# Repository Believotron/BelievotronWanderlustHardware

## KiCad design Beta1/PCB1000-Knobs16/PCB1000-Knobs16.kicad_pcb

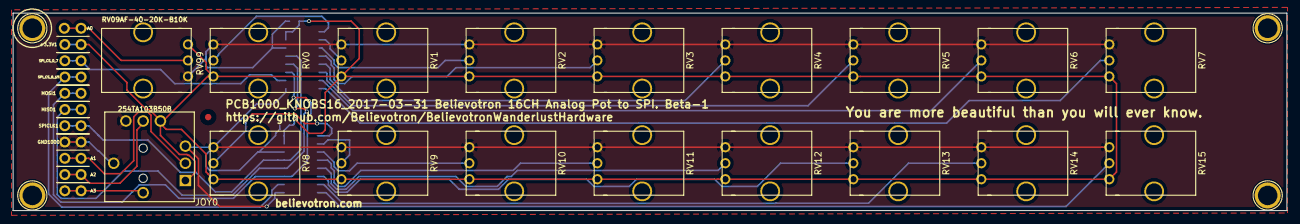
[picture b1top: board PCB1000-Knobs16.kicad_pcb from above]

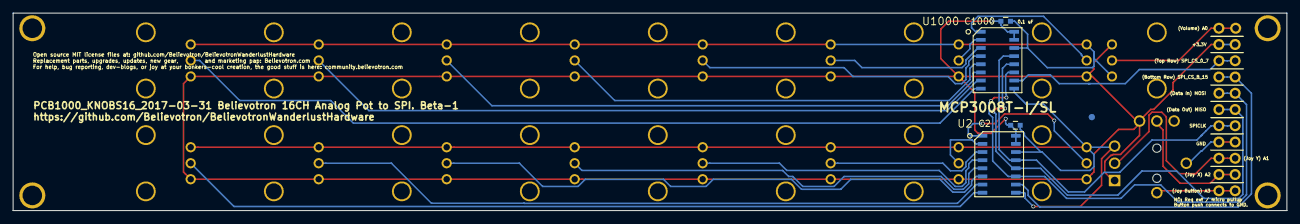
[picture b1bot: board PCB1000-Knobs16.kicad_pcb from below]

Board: 2 copper layers, 199.0 x 30.9 mm, 37 parts (4 on the bottom side), 27 nets.

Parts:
+3.3V1: CONN_01X01; TH_0.1_1x2_Jumper
A0, A0#2, A1, A1#2, A2, A2#2, A3, A3#2: CONN_01X01; single_0.1
C2, C1000: 0.1u; C_0603
GND1000: CONN_01X01; TH_0.1_1x2_Jumper
JOY0: XYJOY; XY_JOY_254TA103B50B
MISO1: CONN_01X01; TH_0.1_1x2_Jumper
MOSI1: CONN_01X01; TH_0.1_1x2_Jumper
RV0, RV1, RV2, RV3, RV4, RV5, RV6, RV7, RV8, RV9, RV10, RV11, RV12, RV13, RV14, RV15, RV99: POT; RV09AF-40-20K-B10K
SPICLK1: CONN_01X01; TH_0.1_1x2_Jumper
SPI_CS_0_7, SPI_CS_8_15: CONN_01X01; TH_0.1_1x2_Jumper
U2, U1000: MCP3008T-I/SL; SOIC-16

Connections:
+3V3: +3.3V1.1, C2.1, C1000.1, JOY0.R1.1, JOY0.R2.1, RV0.1, RV1.1, RV2.1, RV3.1, RV4.1, RV5.1, RV6.1, RV7.1, RV8.1, RV9.1, RV10.1, RV11.1, RV12.1, RV13.1, RV14.1, RV15.1, RV99.1, U2.15, U2.16, U1000.15, U1000.16
/CS_LED_8_15: SPI_CS_8_15.1, U2.10
/CS_R0_7: SPI_CS_0_7.1, U1000.10
/MISO: MISO1.1, U2.12, U1000.12
/MOSI: MOSI1.1, U2.11, U1000.11
/P0: RV0.2, U1000.1
/P1: RV1.2, U1000.2
/P2: RV2.2, U1000.3
/P3: RV3.2, U1000.4
/P4: RV4.2, U1000.5
/P5: RV5.2, U1000.6
/P6: RV6.2, U1000.7
/P7: RV7.2, U1000.8
/P8: RV8.2, U2.1
/P9: RV9.2, U2.2
/P10: RV10.2, U2.3
/P11: RV11.2, U2.4
/P12: RV12.2, U2.5
/P13: RV13.2, U2.6
/P14: RV14.2, U2.7
/P15: RV15.2, U2.8
/SPICLK: SPICLK1.1, U2.13, U1000.13
/VOLUME: A0.1, A0#2.1, RV99.2
GND: C2.2, C1000.2, GND1000.1, JOY0.R1.3, JOY0.R2.3, JOY0.S1.1, RV0.3, RV1.3, RV2.3, RV3.3, RV4.3, RV5.3, RV6.3, RV7.3, RV8.3, RV9.3, RV10.3, RV11.3, RV12.3, RV13.3, RV14.3, RV15.3, RV99.3, U2.9, U2.14, U1000.9, U1000.14
unnamed: A1.1, A1#2.1, JOY0.R1.2
unnamed: A2.1, A2#2.1, JOY0.R2.2
unnamed: A3.1, A3#2.1, JOY0.S1.2

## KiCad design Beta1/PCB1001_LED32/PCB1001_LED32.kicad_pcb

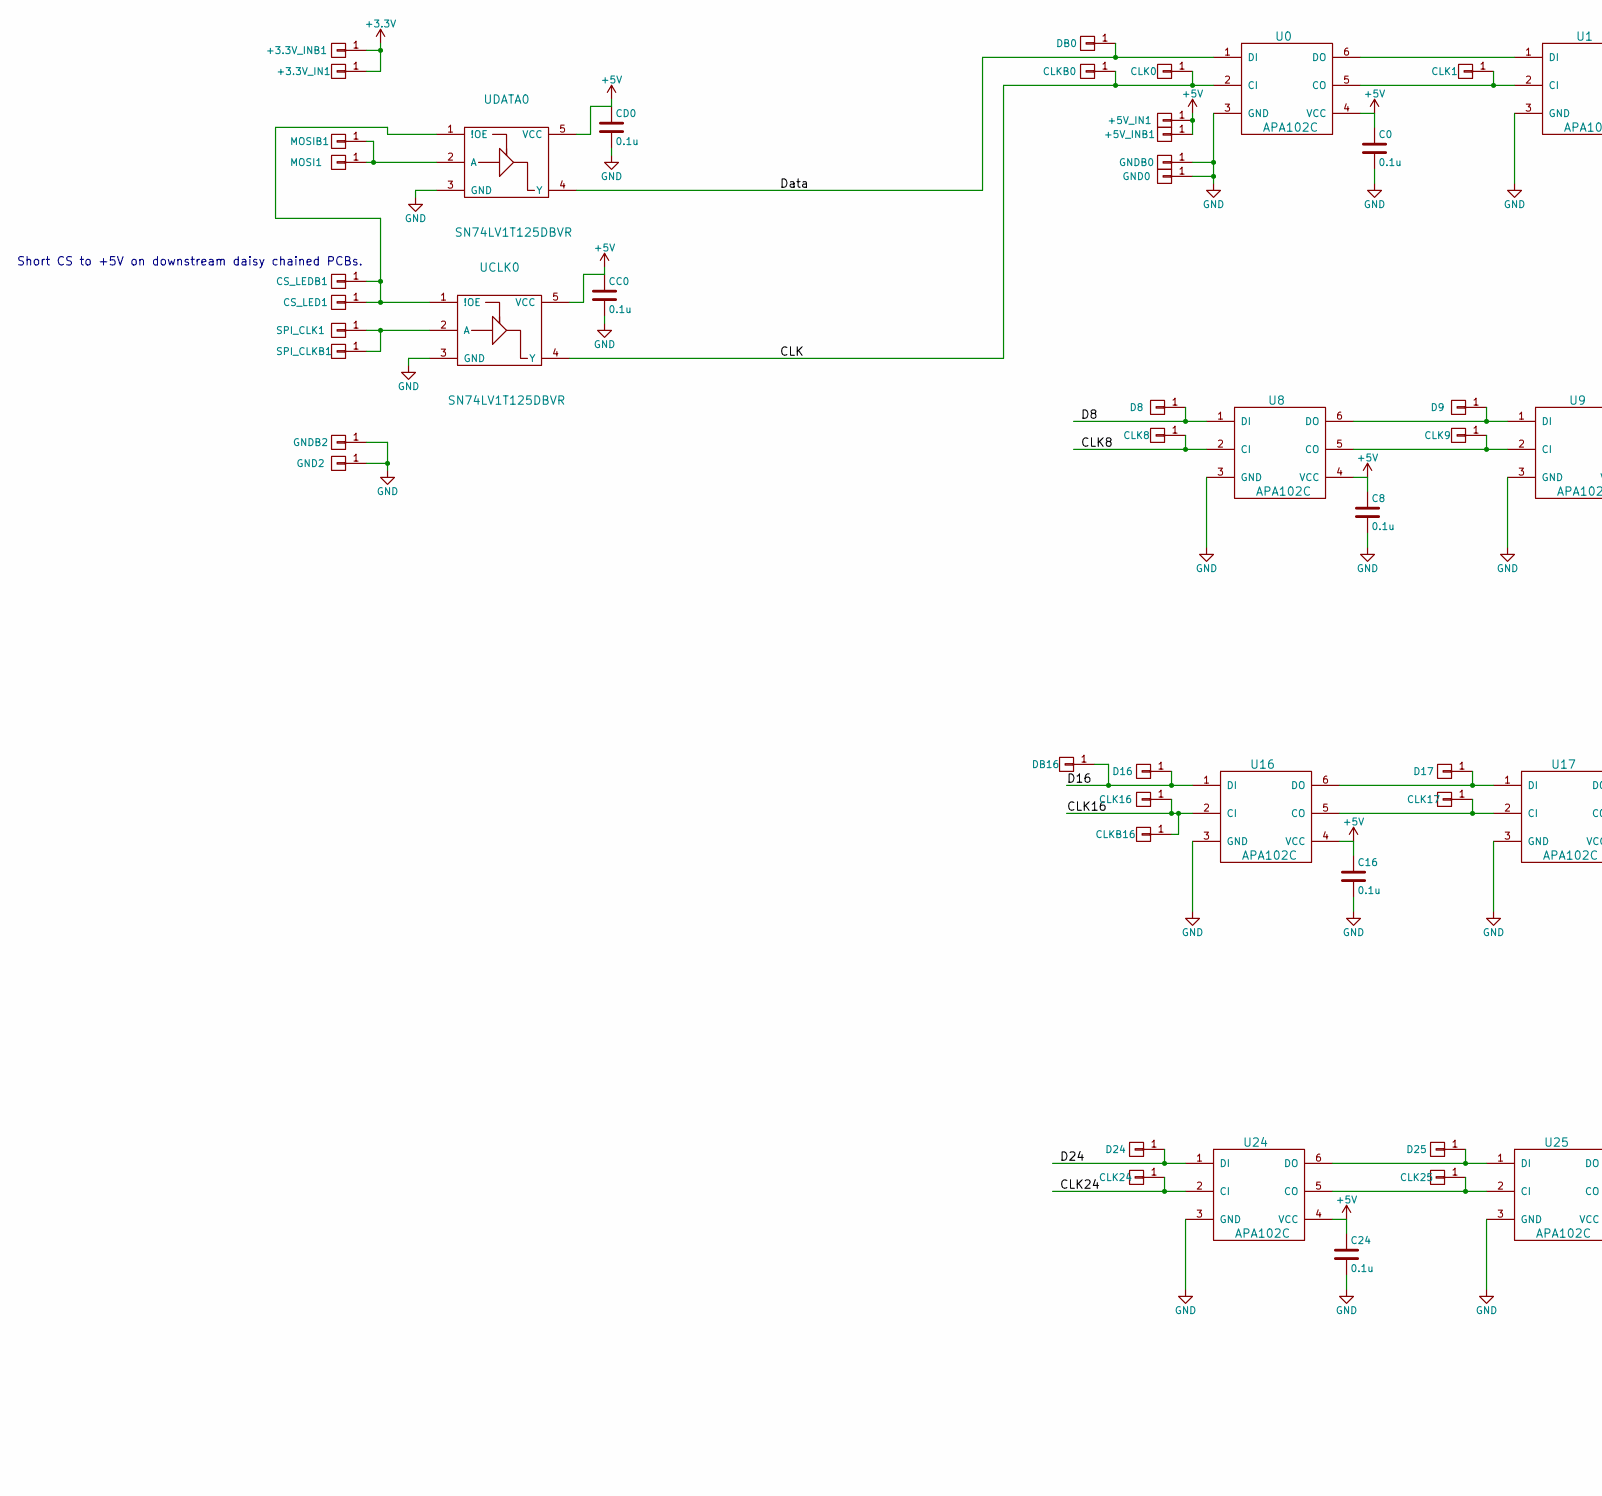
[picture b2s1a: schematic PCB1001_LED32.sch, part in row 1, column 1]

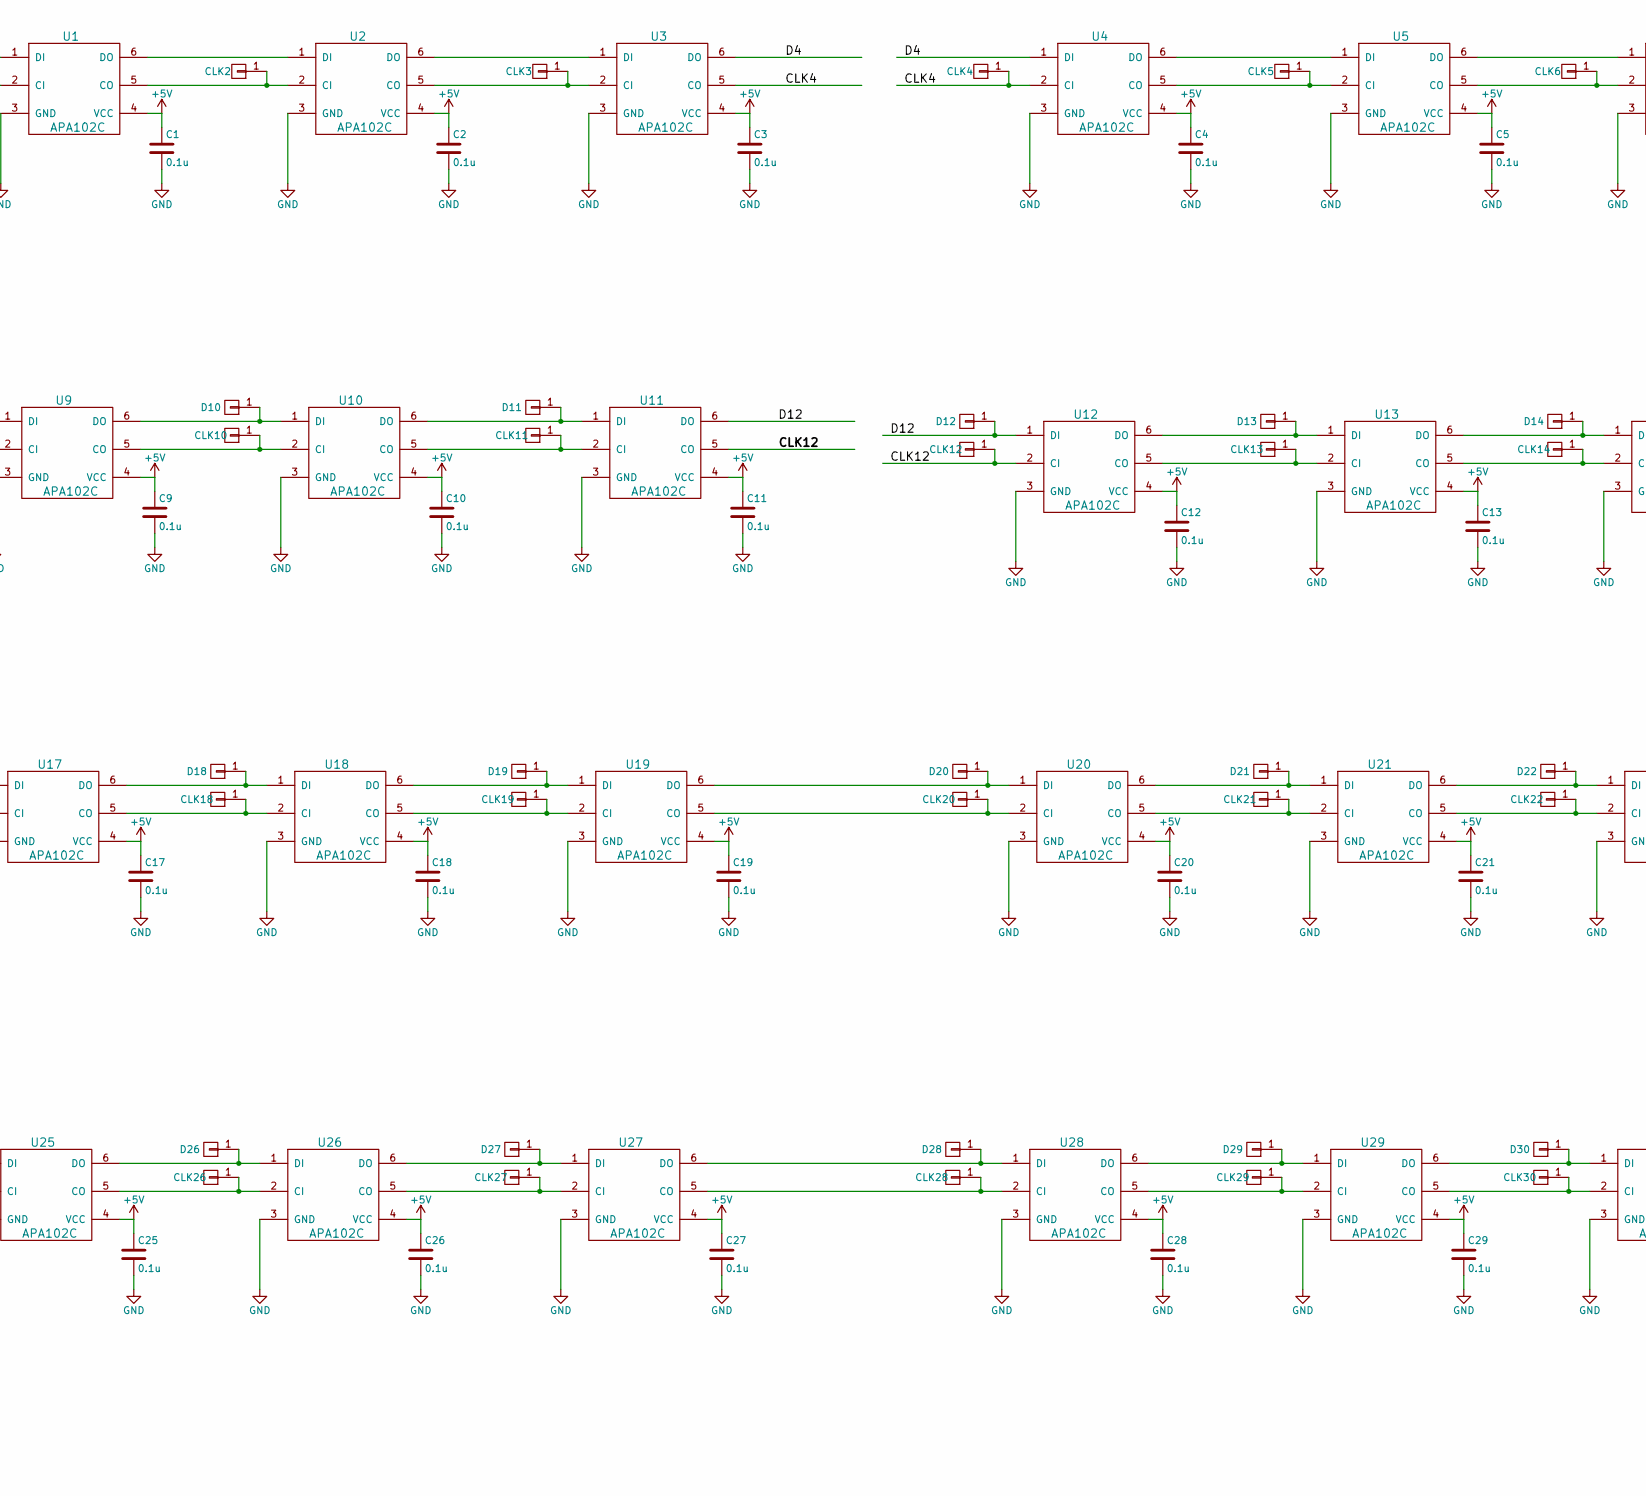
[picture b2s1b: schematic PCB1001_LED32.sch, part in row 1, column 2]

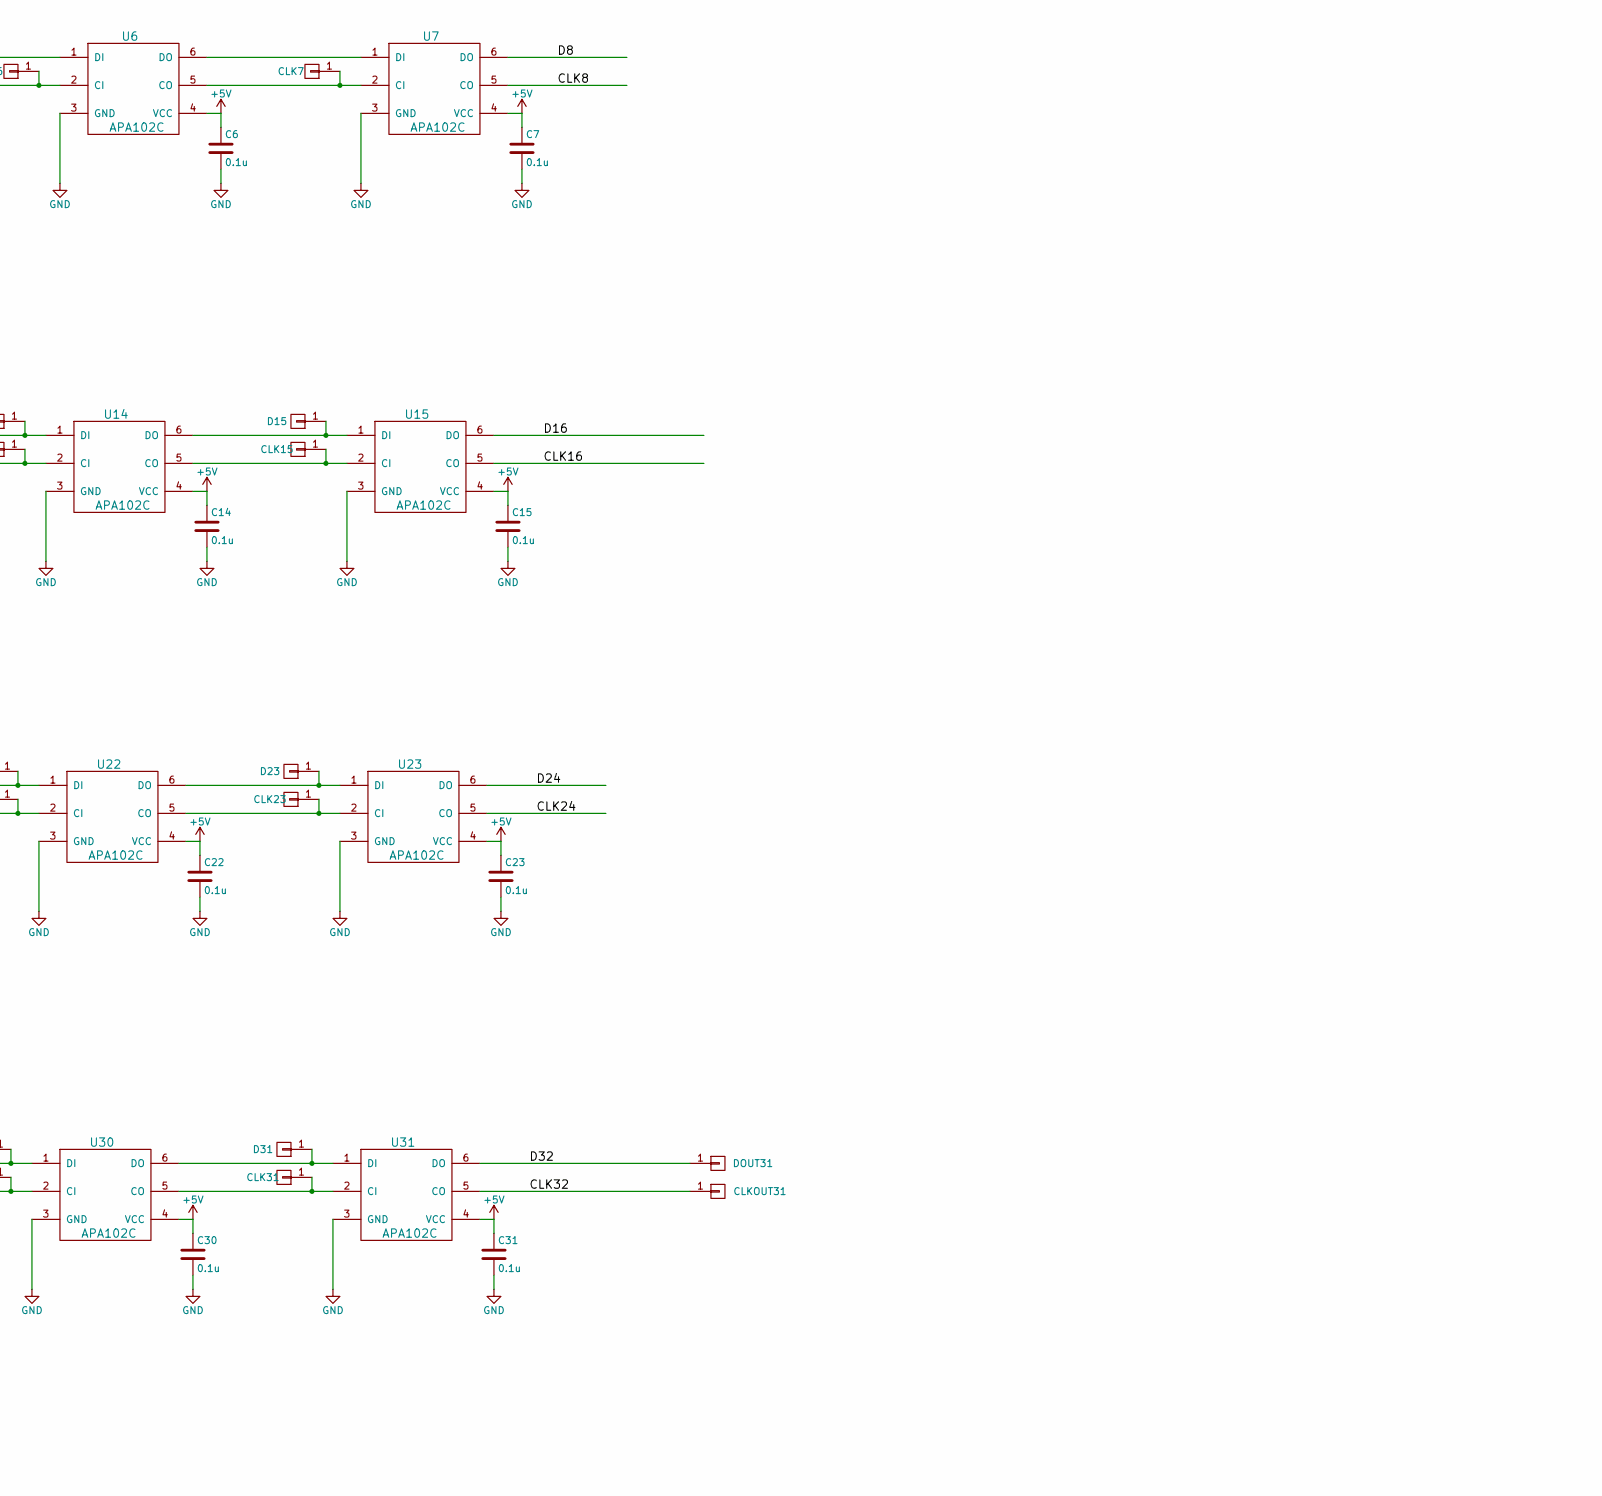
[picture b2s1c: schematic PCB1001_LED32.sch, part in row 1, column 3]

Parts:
+3.3V_IN1, +3.3V_INB1, +5V_IN1, +5V_INB1: CONN_01X01; single_0.1; MPN ON_PCB
C0, C1, C2, C3, C4, C5, C6, C7, C8, C9, C10, C11, C12, C13, C14, C15, C16, C17, C18, C19, C20, C21, C22, C23, C24, C25, C26, C27, C28, C29, C30, C31: 0.1u; C_0603; MPN CC0603KRX7R9BB104
CC0: 0.1u; C_0603; MPN CC0603KRX7R9BB104
CD0: 0.1u; C_0603; MPN CC0603KRX7R9BB104
CLK0, CLK16: CONN_01X01; single_0.1; MPN ON_PCB
CLK1, CLK2, CLK3, CLK4, CLK5, CLK6, CLK7, CLK8, CLK9, CLK10, CLK11, CLK12, CLK13, CLK14, CLK15, CLK17, CLK18, CLK19, CLK20, CLK21, CLK22, CLK23, CLK24, CLK25, CLK26, CLK27, CLK28, CLK29, CLK30, CLK31: CONN_01X01; TESTPAD; MPN ON_PCB
CLKB0, CLKB16: CONN_01X01; single_0.1; MPN ON_PCB
CLKOUT31: CONN_01X01; single_0.1; MPN ON_PCB
CS_LED1: CONN_01X01; single_0.1; MPN ON_PCB
CS_LEDB1: CONN_01X01; single_0.1; MPN ON_PCB
D8, D9, D10, D11, D12, D13, D14, D15, D17, D18, D19, D20, D21, D22, D23, D24, D25, D26, D27, D28, D29, D30, D31: CONN_01X01; TESTPAD; MPN ON_PCB
D16: CONN_01X01; single_0.1; MPN ON_PCB
DB0, DB16: CONN_01X01; single_0.1; MPN ON_PCB
DOUT31: CONN_01X01; single_0.1; MPN ON_PCB
GND0, GND2: CONN_01X01; single_0.1; MPN ON_PCB
GNDB0, GNDB2: CONN_01X01; single_0.1; MPN ON_PCB
MOSI1: CONN_01X01; single_0.1; MPN ON_PCB
MOSIB1: CONN_01X01; single_0.1; MPN ON_PCB
SPI_CLK1: CONN_01X01; single_0.1; MPN ON_PCB
SPI_CLKB1: CONN_01X01; single_0.1; MPN ON_PCB
U0, U1, U2, U3, U4, U5, U6, U7, U8, U9, U10, U11, U12, U13, U14, U15, U16, U17, U18, U19, U20, U21, U22, U23, U24, U25, U26, U27, U28, U29, U30, U31: APA102C; PLCC6-1.6x4.2_LED; MPN APA102C
UCLK0: SN74LV1T125DBVR; SOT23-5; MPN SN74LV1T125DBVR
UDATA0: SN74LV1T125DBVR; SOT23-5; MPN SN74LV1T125DBVR

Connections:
+3V3: +3.3V_IN1.1, +3.3V_INB1.1
+5V: +5V_IN1.1, +5V_INB1.1, C0.1, C1.1, C2.1, C3.1, C4.1, C5.1, C6.1, C7.1, C8.1, C9.1, C10.1, C11.1, C12.1, C13.1, C14.1, C15.1, C16.1, C17.1, C18.1, C19.1, C20.1, C21.1, C22.1, C23.1, C24.1, C25.1, C26.1, C27.1, C28.1, C29.1, C30.1, C31.1, CC0.1, CD0.1, U0.4 (VCC), U1.4 (VCC), U2.4 (VCC), U3.4 (VCC), U4.4 (VCC), U5.4 (VCC), U6.4 (VCC), U7.4 (VCC), U8.4 (VCC), U9.4 (VCC), U10.4 (VCC), U11.4 (VCC), U12.4 (VCC), U13.4 (VCC), U14.4 (VCC), U15.4 (VCC), U16.4 (VCC), U17.4 (VCC), U18.4 (VCC), U19.4 (VCC), U20.4 (VCC), U21.4 (VCC), U22.4 (VCC), U23.4 (VCC), U24.4 (VCC), U25.4 (VCC), U26.4 (VCC), U27.4 (VCC), U28.4 (VCC), U29.4 (VCC), U30.4 (VCC), U31.4 (VCC), UCLK0.5 (VCC), UDATA0.5 (VCC)
/CLK: CLK0.1, CLKB0.1, U0.2 (CI), UCLK0.4 (Y)
/CLK4: CLK4.1, U3.5 (CO), U4.2 (CI)
/CLK8: CLK8.1, U7.5 (CO), U8.2 (CI)
/CLK12: CLK12.1, U11.5 (CO), U12.2 (CI)
/CLK16: CLK16.1, CLKB16.1, U15.5 (CO), U16.2 (CI)
/CLK24: CLK24.1, U23.5 (CO), U24.2 (CI)
/CLK32: CLKOUT31.1, U31.5 (CO)
/D4: U3.6 (DO), U4.1 (DI); also elsewhere on the board
/D8: D8.1, U7.6 (DO), U8.1 (DI)
/D12: D12.1, U11.6 (DO), U12.1 (DI)
/D16: D16.1, DB16.1, U15.6 (DO), U16.1 (DI)
/D24: D24.1, U23.6 (DO), U24.1 (DI)
/D32: DOUT31.1, U31.6 (DO)
/Data: DB0.1, U0.1 (DI), UDATA0.4 (Y); also elsewhere on the board
GND: C0.2, C1.2, C2.2, C3.2, C4.2, C5.2, C6.2, C7.2, C8.2, C9.2, C10.2, C11.2, C12.2, C13.2, C14.2, C15.2, C16.2, C17.2, C18.2, C19.2, C20.2, C21.2, C22.2, C23.2, C24.2, C25.2, C26.2, C27.2, C28.2, C29.2, C30.2, C31.2, CC0.2, CD0.2, GND0.1, GND2.1, GNDB0.1, GNDB2.1, U0.3 (GND), U1.3 (GND), U2.3 (GND), U3.3 (GND), U4.3 (GND), U5.3 (GND), U6.3 (GND), U7.3 (GND), U8.3 (GND), U9.3 (GND), U10.3 (GND), U11.3 (GND), U12.3 (GND), U13.3 (GND), U14.3 (GND), U15.3 (GND), U16.3 (GND), U17.3 (GND), U18.3 (GND), U19.3 (GND), U20.3 (GND), U21.3 (GND), U22.3 (GND), U23.3 (GND), U24.3 (GND), U25.3 (GND), U26.3 (GND), U27.3 (GND), U28.3 (GND), U29.3 (GND), U30.3 (GND), U31.3 (GND), UCLK0.3 (GND), UDATA0.3 (GND); also elsewhere on the board
unnamed: CLK1.1, U0.5 (CO), U1.2 (CI)
unnamed: CLK2.1, U1.5 (CO), U2.2 (CI)
unnamed: CLK3.1, U2.5 (CO), U3.2 (CI)
unnamed: CLK5.1, U4.5 (CO), U5.2 (CI)
unnamed: CLK6.1, U5.5 (CO), U6.2 (CI)
unnamed: CLK7.1, U6.5 (CO), U7.2 (CI)
unnamed: CLK9.1, U8.5 (CO), U9.2 (CI)
unnamed: CLK10.1, U9.5 (CO), U10.2 (CI)
unnamed: CLK11.1, U10.5 (CO), U11.2 (CI)
unnamed: CLK13.1, U12.5 (CO), U13.2 (CI)
unnamed: CLK14.1, U13.5 (CO), U14.2 (CI)
unnamed: CLK15.1, U14.5 (CO), U15.2 (CI)
unnamed: CLK17.1, U16.5 (CO), U17.2 (CI)
unnamed: CLK18.1, U17.5 (CO), U18.2 (CI)
unnamed: CLK19.1, U18.5 (CO), U19.2 (CI)
unnamed: CLK20.1, U19.5 (CO), U20.2 (CI)
unnamed: CLK21.1, U20.5 (CO), U21.2 (CI)
unnamed: CLK22.1, U21.5 (CO), U22.2 (CI)
unnamed: CLK23.1, U22.5 (CO), U23.2 (CI)
unnamed: CLK25.1, U24.5 (CO), U25.2 (CI)
unnamed: CLK26.1, U25.5 (CO), U26.2 (CI)
unnamed: CLK27.1, U26.5 (CO), U27.2 (CI)
unnamed: CLK28.1, U27.5 (CO), U28.2 (CI)
unnamed: CLK29.1, U28.5 (CO), U29.2 (CI)
unnamed: CLK30.1, U29.5 (CO), U30.2 (CI)
unnamed: CLK31.1, U30.5 (CO), U31.2 (CI)
unnamed 43: CS_LED1.1, CS_LEDB1.1, UCLK0.1 (!OE), UDATA0.1 (!OE); also elsewhere on the board
unnamed 44: U0.6 (DO), U1.1 (DI); also elsewhere on the board
unnamed 45: U1.6 (DO), U2.1 (DI); also elsewhere on the board
unnamed 46: U2.6 (DO), U3.1 (DI); also elsewhere on the board
unnamed 47: U4.6 (DO), U5.1 (DI); also elsewhere on the board
unnamed 48: U5.6 (DO), U6.1 (DI); also elsewhere on the board
unnamed 49: U6.6 (DO), U7.1 (DI); also elsewhere on the board
unnamed: D9.1, U8.6 (DO), U9.1 (DI)
unnamed: D10.1, U9.6 (DO), U10.1 (DI)
unnamed: D11.1, U10.6 (DO), U11.1 (DI)
unnamed: D13.1, U12.6 (DO), U13.1 (DI)
unnamed: D14.1, U13.6 (DO), U14.1 (DI)
unnamed: D15.1, U14.6 (DO), U15.1 (DI)
unnamed: D17.1, U16.6 (DO), U17.1 (DI)
unnamed: D18.1, U17.6 (DO), U18.1 (DI)
unnamed: D19.1, U18.6 (DO), U19.1 (DI)
unnamed: D20.1, U19.6 (DO), U20.1 (DI)
unnamed: D21.1, U20.6 (DO), U21.1 (DI)
unnamed: D22.1, U21.6 (DO), U22.1 (DI)
unnamed: D23.1, U22.6 (DO), U23.1 (DI)
unnamed: D25.1, U24.6 (DO), U25.1 (DI)
unnamed: D26.1, U25.6 (DO), U26.1 (DI)
unnamed: D27.1, U26.6 (DO), U27.1 (DI)
unnamed: D28.1, U27.6 (DO), U28.1 (DI)
unnamed: D29.1, U28.6 (DO), U29.1 (DI)
unnamed: D30.1, U29.6 (DO), U30.1 (DI)
unnamed: D31.1, U30.6 (DO), U31.1 (DI)
unnamed: MOSI1.1, MOSIB1.1, UDATA0.2 (A)
unnamed: SPI_CLK1.1, SPI_CLKB1.1, UCLK0.2 (A)

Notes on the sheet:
Files and Open source MIT License: github.com/Believotron/BelievotronWanderlustHardware Marketing Pap: Believotron.com The good stuff: community.believotron.com
Believotron Wanderlust 32 CH RGB LED PCB
2017-03-31
DATE
Author: Dazzling Duke of Lazers
Short CS to +5V on downstream daisy chained PCBs.

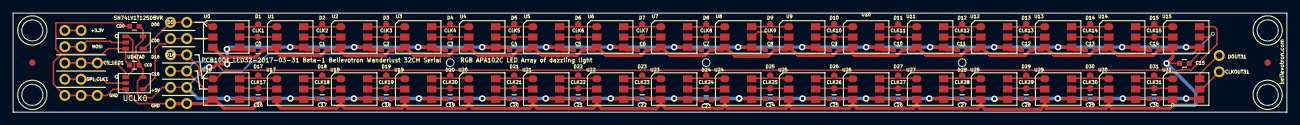
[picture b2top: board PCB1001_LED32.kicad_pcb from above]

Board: 2 copper layers, 199.0 x 15.5 mm, 153 parts (0 on the bottom side), 72 nets.

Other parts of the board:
CS_LED1#2: CONN_01X01; single_0.1
D0: CONN_01X01; single_0.1
D1, D2, D3, D4, D5, D6, D7: CONN_01X01; TESTPAD
GNDB2#2: CONN_01X01; single_0.1

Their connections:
/D4: D4.1; also elsewhere on the board
/Data: D0.1; also elsewhere on the board
GND: GNDB2#2.1; also elsewhere on the board
unnamed 43: CS_LED1#2.1; also elsewhere on the board
unnamed 44: D1.1; also elsewhere on the board
unnamed 45: D2.1; also elsewhere on the board
unnamed 46: D3.1; also elsewhere on the board
unnamed 47: D5.1; also elsewhere on the board
unnamed 48: D6.1; also elsewhere on the board
unnamed 49: D7.1; also elsewhere on the board

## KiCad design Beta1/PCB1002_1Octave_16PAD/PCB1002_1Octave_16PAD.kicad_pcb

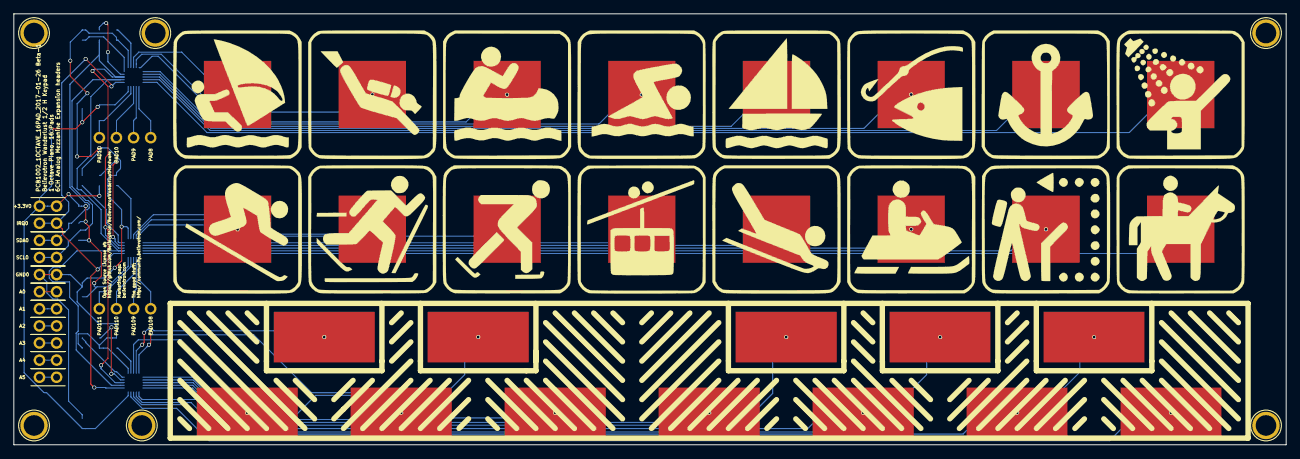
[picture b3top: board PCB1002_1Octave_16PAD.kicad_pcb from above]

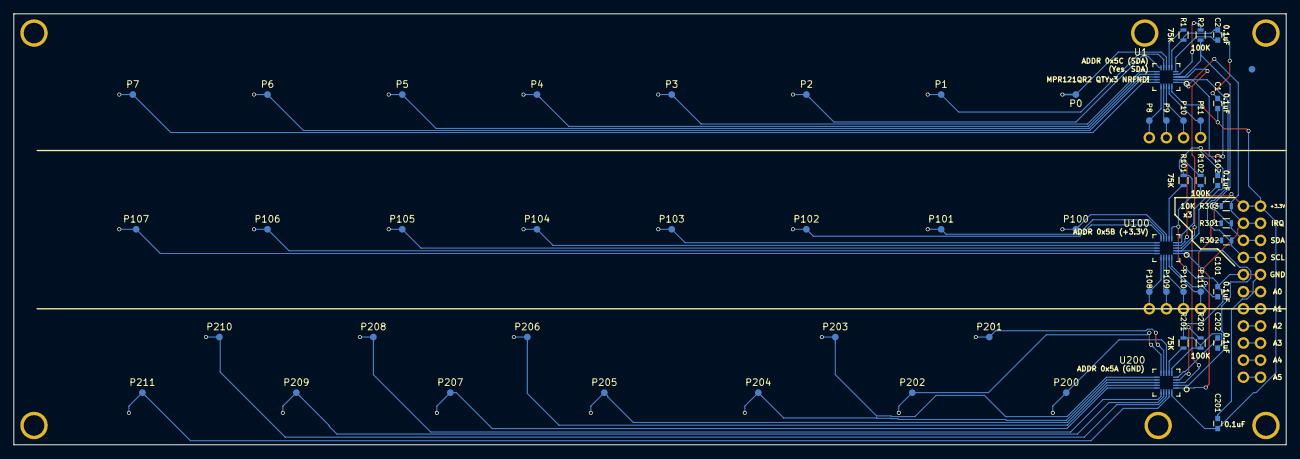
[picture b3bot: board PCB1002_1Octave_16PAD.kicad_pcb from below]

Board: 2 copper layers, 188.9 x 64.0 mm, 90 parts (54 on the bottom side), 50 nets.

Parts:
+3.3V0: CONN_01X01; TH_0.1_1x2_Jumper
A0, A1, A2, A3, A4, A5: CONN_01X01; TH_0.1_1x2_Jumper
C1, C101, C201: CC0603KRX7R9BB104; C_0603
C2, C102, C202: 0.1uf; C_0603
GND0: CONN_01X01; TH_0.1_1x2_Jumper
IRQ0: CONN_01X01; TH_0.1_1x2_Jumper
P0, P1, P2, P3, P4, P5, P6, P7, P8, P9, P10, P11, P100, P101, P102, P103, P104, P105, P106, P107, P108, P109, P110, P111, P200, P201, P202, P203, P204, P205, P206, P207, P208, P209, P210, P211: CONN_01X01; TESTPAD
PAD0, PAD1, PAD2, PAD3, PAD4, PAD5, PAD6, PAD7, PAD100, PAD101, PAD102, PAD103, PAD104, PAD105, PAD106, PAD107: TOUCHPAD_10CM; TOUCH_PAD_10CM
PAD8, PAD9, PAD10, PAD11, PAD108, PAD109, PAD110, PAD111: CONN_01X01; single_0.1
R1, R101, R201: 75K; R_0603
R2, R102, R202: 100K; R_0603
R301, R302, R303: 10K; R_0603
SCL0: CONN_01X01; TH_0.1_1x2_Jumper
SDA0: CONN_01X01; TH_0.1_1x2_Jumper
U1, U100, U200: MPR121QR2; QFN-20-1EP_3x3mm_Pitch0.40mm
UKEY0: KEYBOARD_1OCT; Keyboard_1_Octave_20CM

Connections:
+3V3: +3.3V0.1, C1.1, C101.1, C201.1, R102.1, R301.1, R302.1, R303.1, U1.20, U100.20, U200.20
/IRQ: IRQ0.1, R303.2, U1.1, U100.1, U200.1
/PAD0: P0.1, PAD0.1, U1.8
/PAD1: P1.1, PAD1.1, U1.9
/PAD2: P2.1, PAD2.1, U1.10
/PAD3: P3.1, PAD3.1, U1.11
/PAD4: P4.1, PAD4.1, U1.12
/PAD5: P5.1, PAD5.1, U1.13
/PAD6: P6.1, PAD6.1, U1.14
/PAD7: P7.1, PAD7.1, U1.15
/SCL: R302.2, SCL0.1, U1.2, U100.2, U200.2
/SDA: R2.1, R301.2, SDA0.1, U1.3, U100.3, U200.3
GND: C1.2, C2.2, C101.2, C102.2, C201.2, C202.2, GND0.1, R1.2, R101.2, R201.2, R202.1, U1.6, U100.6, U200.6
unnamed: C2.1, U1.5
unnamed: C102.1, U100.5
unnamed: C202.1, U200.5
unnamed: P8.1, PAD8.1, U1.16
unnamed: P9.1, PAD9.1, U1.17
unnamed: P10.1, PAD10.1, U1.18
unnamed: P11.1, PAD11.1, U1.19
unnamed: P100.1, PAD100.1, U100.8
unnamed: P101.1, PAD101.1, U100.9
unnamed: P102.1, PAD102.1, U100.10
unnamed: P103.1, PAD103.1, U100.11
unnamed: P104.1, PAD104.1, U100.12
unnamed: P105.1, PAD105.1, U100.13
unnamed: P106.1, PAD106.1, U100.14
unnamed: P107.1, PAD107.1, U100.15
unnamed: P108.1, PAD108.1, U100.16
unnamed: P109.1, PAD109.1, U100.17
unnamed: P110.1, PAD110.1, U100.18
unnamed: P111.1, PAD111.1, U100.19
unnamed: P200.1, U200.8, UKEY0.1
unnamed: P201.1, U200.9, UKEY0.2
unnamed: P202.1, U200.10, UKEY0.3
unnamed: P203.1, U200.11, UKEY0.4
unnamed: P204.1, U200.12, UKEY0.5
unnamed: P205.1, U200.13, UKEY0.6
unnamed: P206.1, U200.14, UKEY0.7
unnamed: P207.1, U200.15, UKEY0.8
unnamed: P208.1, U200.16, UKEY0.9
unnamed: P209.1, U200.17, UKEY0.10
unnamed: P210.1, U200.18, UKEY0.11
unnamed: P211.1, U200.19, UKEY0.12
unnamed: R1.1, U1.7
unnamed: R2.2, U1.4
unnamed: R101.1, U100.7
unnamed: R102.2, U100.4
unnamed: R201.1, U200.7
unnamed: R202.2, U200.4

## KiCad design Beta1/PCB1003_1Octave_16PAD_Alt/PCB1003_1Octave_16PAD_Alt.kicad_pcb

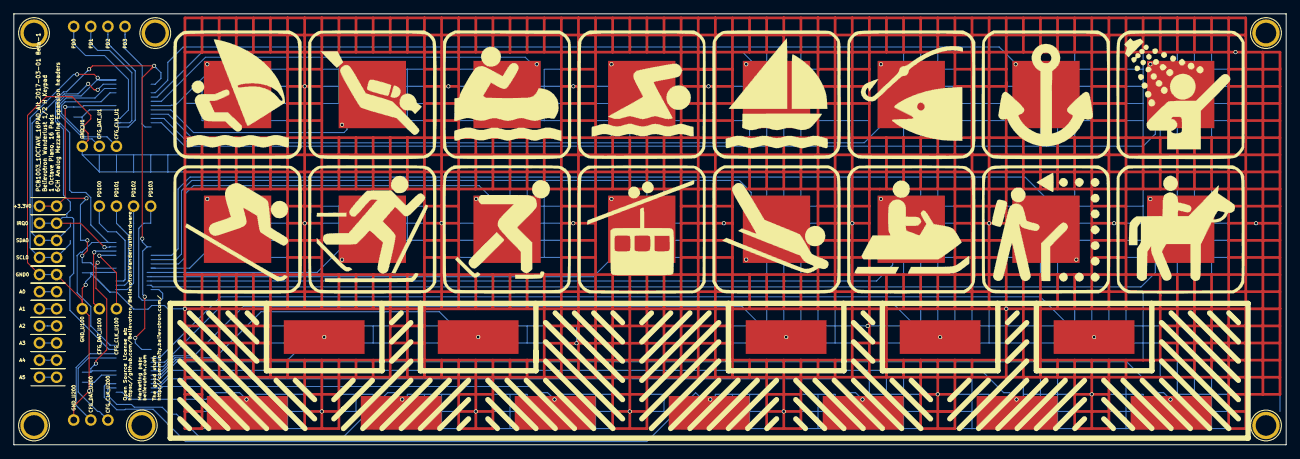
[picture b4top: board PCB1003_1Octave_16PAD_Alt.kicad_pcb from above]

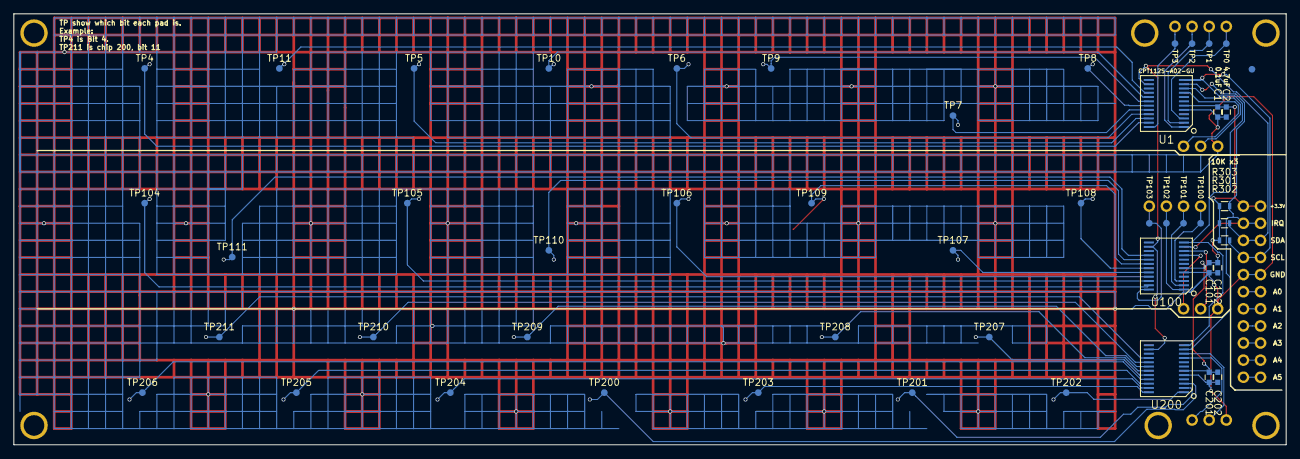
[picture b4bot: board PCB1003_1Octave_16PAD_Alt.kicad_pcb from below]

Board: 2 copper layers, 188.9 x 64.0 mm, 93 parts (48 on the bottom side), 47 nets.

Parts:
+3.3V0: CONN_01X01; TH_0.1_1x2_Jumper
A0, A1, A2, A3, A4, A5: CONN_01X01; TH_0.1_1x2_Jumper
C1, C101, C201: 0.1uf; C_0603
C2, C102, C202: 4.7 uF; C_0603
CFG_CLK_U1, CFG_CLK_U100, CFG_CLK_U200: CONN_01X01; single_0.1
CFG_DAT_U1, CFG_DAT_U100, CFG_DAT_U200: CONN_01X01; single_0.1
GND0: CONN_01X01; TH_0.1_1x2_Jumper
GND_U1, GND_U100, GND_U200: CONN_01X01; single_0.1
IRQ0: CONN_01X01; TH_0.1_1x2_Jumper
PAD0, PAD1, PAD2, PAD3, PAD4, PAD5, PAD6, PAD7, PAD100, PAD101, PAD102, PAD103, PAD104, PAD105, PAD106, PAD107: TOUCHPAD_10CM; TOUCH_PAD_10CM
PD0, PD1, PD2, PD3, PD100, PD101, PD102, PD103: CONN_01X01; single_0.1
R301, R302, R303: 10K; R_0603
SCL0: CONN_01X01; TH_0.1_1x2_Jumper
SDA0: CONN_01X01; TH_0.1_1x2_Jumper
TP0, TP1, TP2, TP3, TP4, TP5, TP6, TP7, TP8, TP9, TP10, TP11, TP100, TP101, TP102, TP103, TP104, TP105, TP106, TP107, TP108, TP109, TP110, TP111, TP200, TP201, TP202, TP203, TP204, TP205, TP206, TP207, TP208, TP209, TP210, TP211: CONN_01X01; TESTPAD
U1, U100, U200: CPT112S; SOIC-24_0.635_1.5x5.2
UKEY0: KEYBOARD_1OCT; Keyboard_1_Octave_20CM_V2

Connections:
+3V3: +3.3V0.1, C1.1, C2.1, C101.1, C102.1, C201.1, C202.1, R301.1, R302.1, R303.1, U1.6, U100.6, U200.6
/CHIP_04: PAD7.1, TP4.1, U1.23
/CHIP_05: PAD5.1, TP5.1, U1.22
/CHIP_06: PAD3.1, TP6.1, U1.21
/CHIP_07: PAD1.1, TP7.1, U1.20
/CHIP_08: PAD0.1, TP8.1, U1.19
/CHIP_09: PAD2.1, TP9.1, U1.18
/CHIP_10: PAD4.1, TP10.1, U1.17
/CHIP_11: PAD6.1, TP11.1, U1.16
/CHIP_104: PAD107.1, TP104.1, U100.23
/CHIP_105: PAD105.1, TP105.1, U100.22
/CHIP_106: PAD103.1, TP106.1, U100.21
/CHIP_107: PAD101.1, TP107.1, U100.20
/CHIP_108: PAD100.1, TP108.1, U100.19
/CHIP_109: PAD102.1, TP109.1, U100.18
/CHIP_110: PAD104.1, TP110.1, U100.17
/CHIP_111: PAD106.1, TP111.1, U100.16
/CHIP_200: TP200.1, U200.3, UKEY0.6
/CHIP_201: TP201.1, U200.2, UKEY0.3
/CHIP_202: TP202.1, U200.1, UKEY0.1
/CHIP_203: TP203.1, U200.24, UKEY0.5
/CHIP_204: TP204.1, U200.23, UKEY0.8
/CHIP_205: TP205.1, U200.22, UKEY0.10
/CHIP_206: TP206.1, U200.21, UKEY0.12
/CHIP_207: TP207.1, U200.20, UKEY0.2
/CHIP_208: TP208.1, U200.19, UKEY0.4
/CHIP_209: TP209.1, U200.18, UKEY0.7
/CHIP_210: TP210.1, U200.17, UKEY0.9
/CHIP_211: TP211.1, U200.16, UKEY0.11
/IRQ: IRQ0.1, R303.2, U1.11, U100.11, U200.11
/SCL: R302.2, SCL0.1, U1.12, U100.12, U200.12
/SDA: R301.2, SDA0.1, U1.14, U100.14, U200.14
GND: C1.2, C2.2, C101.2, C102.2, C201.2, C202.2, GND0.1, GND_U1.1, GND_U100.1, GND_U200.1, U1.5, U100.5, U200.5
unnamed: CFG_CLK_U1.1, U1.9
unnamed: CFG_CLK_U100.1, U100.9
unnamed: CFG_CLK_U200.1, U200.9
unnamed: CFG_DAT_U1.1, U1.10
unnamed: CFG_DAT_U100.1, U100.10
unnamed: CFG_DAT_U200.1, U200.10
unnamed: PD0.1, TP0.1, U1.3
unnamed: PD1.1, TP1.1, U1.2
unnamed: PD2.1, TP2.1, U1.1
unnamed: PD3.1, TP3.1, U1.24
unnamed: PD100.1, TP100.1, U100.3
unnamed: PD101.1, TP101.1, U100.2
unnamed: PD102.1, TP102.1, U100.1
unnamed: PD103.1, TP103.1, U100.24

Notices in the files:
Beta1/PCB1002_1Octave_16PAD/PCB1002_1Octave_16PAD.kicad_pcb:
Open Source License at:
https://github.com/Believotron/BelievotronWanderlustHardware
